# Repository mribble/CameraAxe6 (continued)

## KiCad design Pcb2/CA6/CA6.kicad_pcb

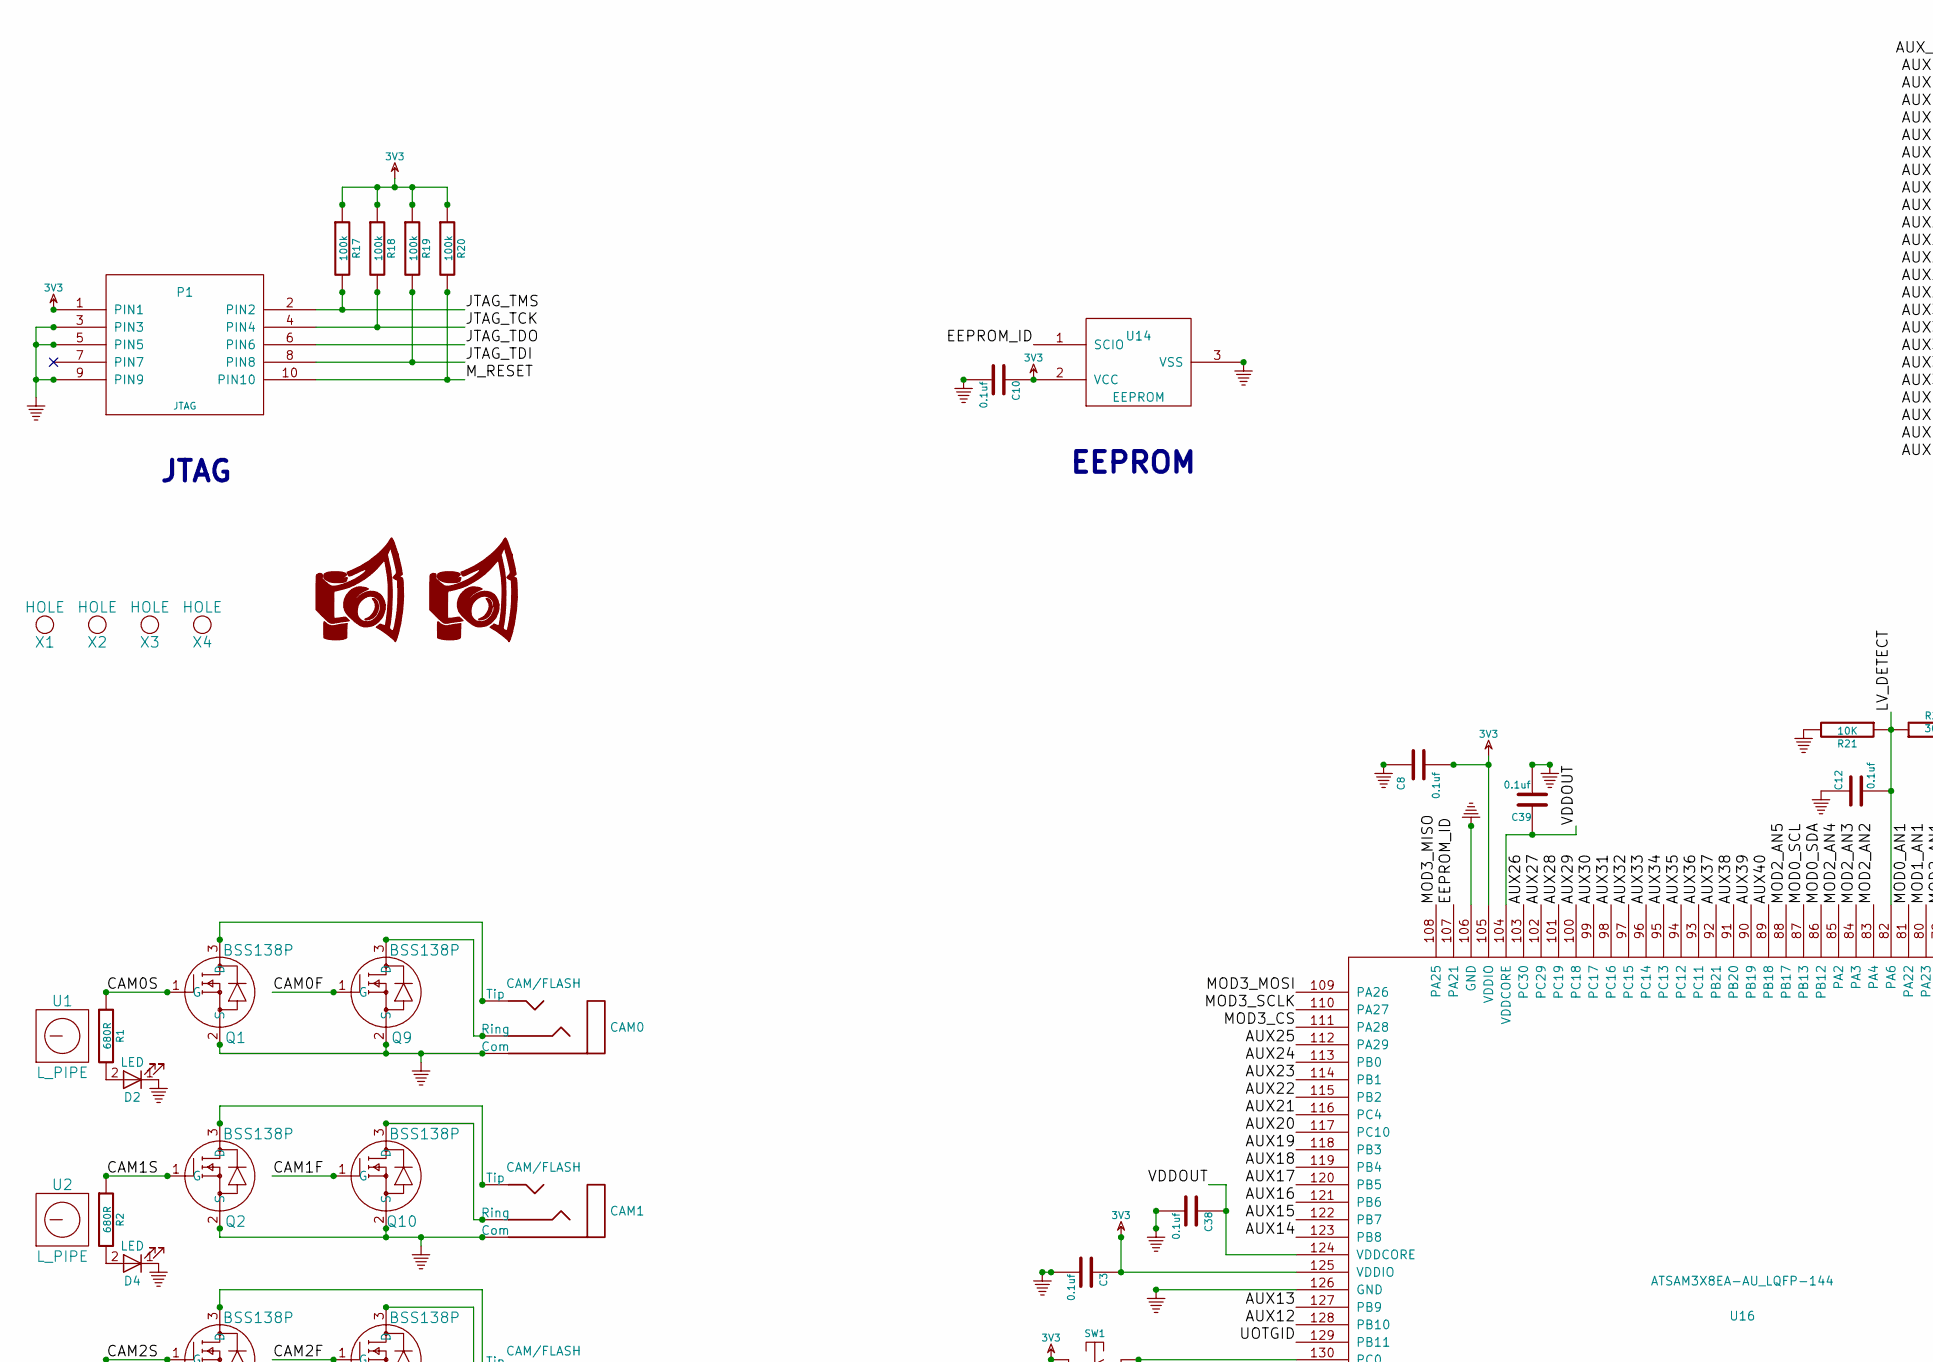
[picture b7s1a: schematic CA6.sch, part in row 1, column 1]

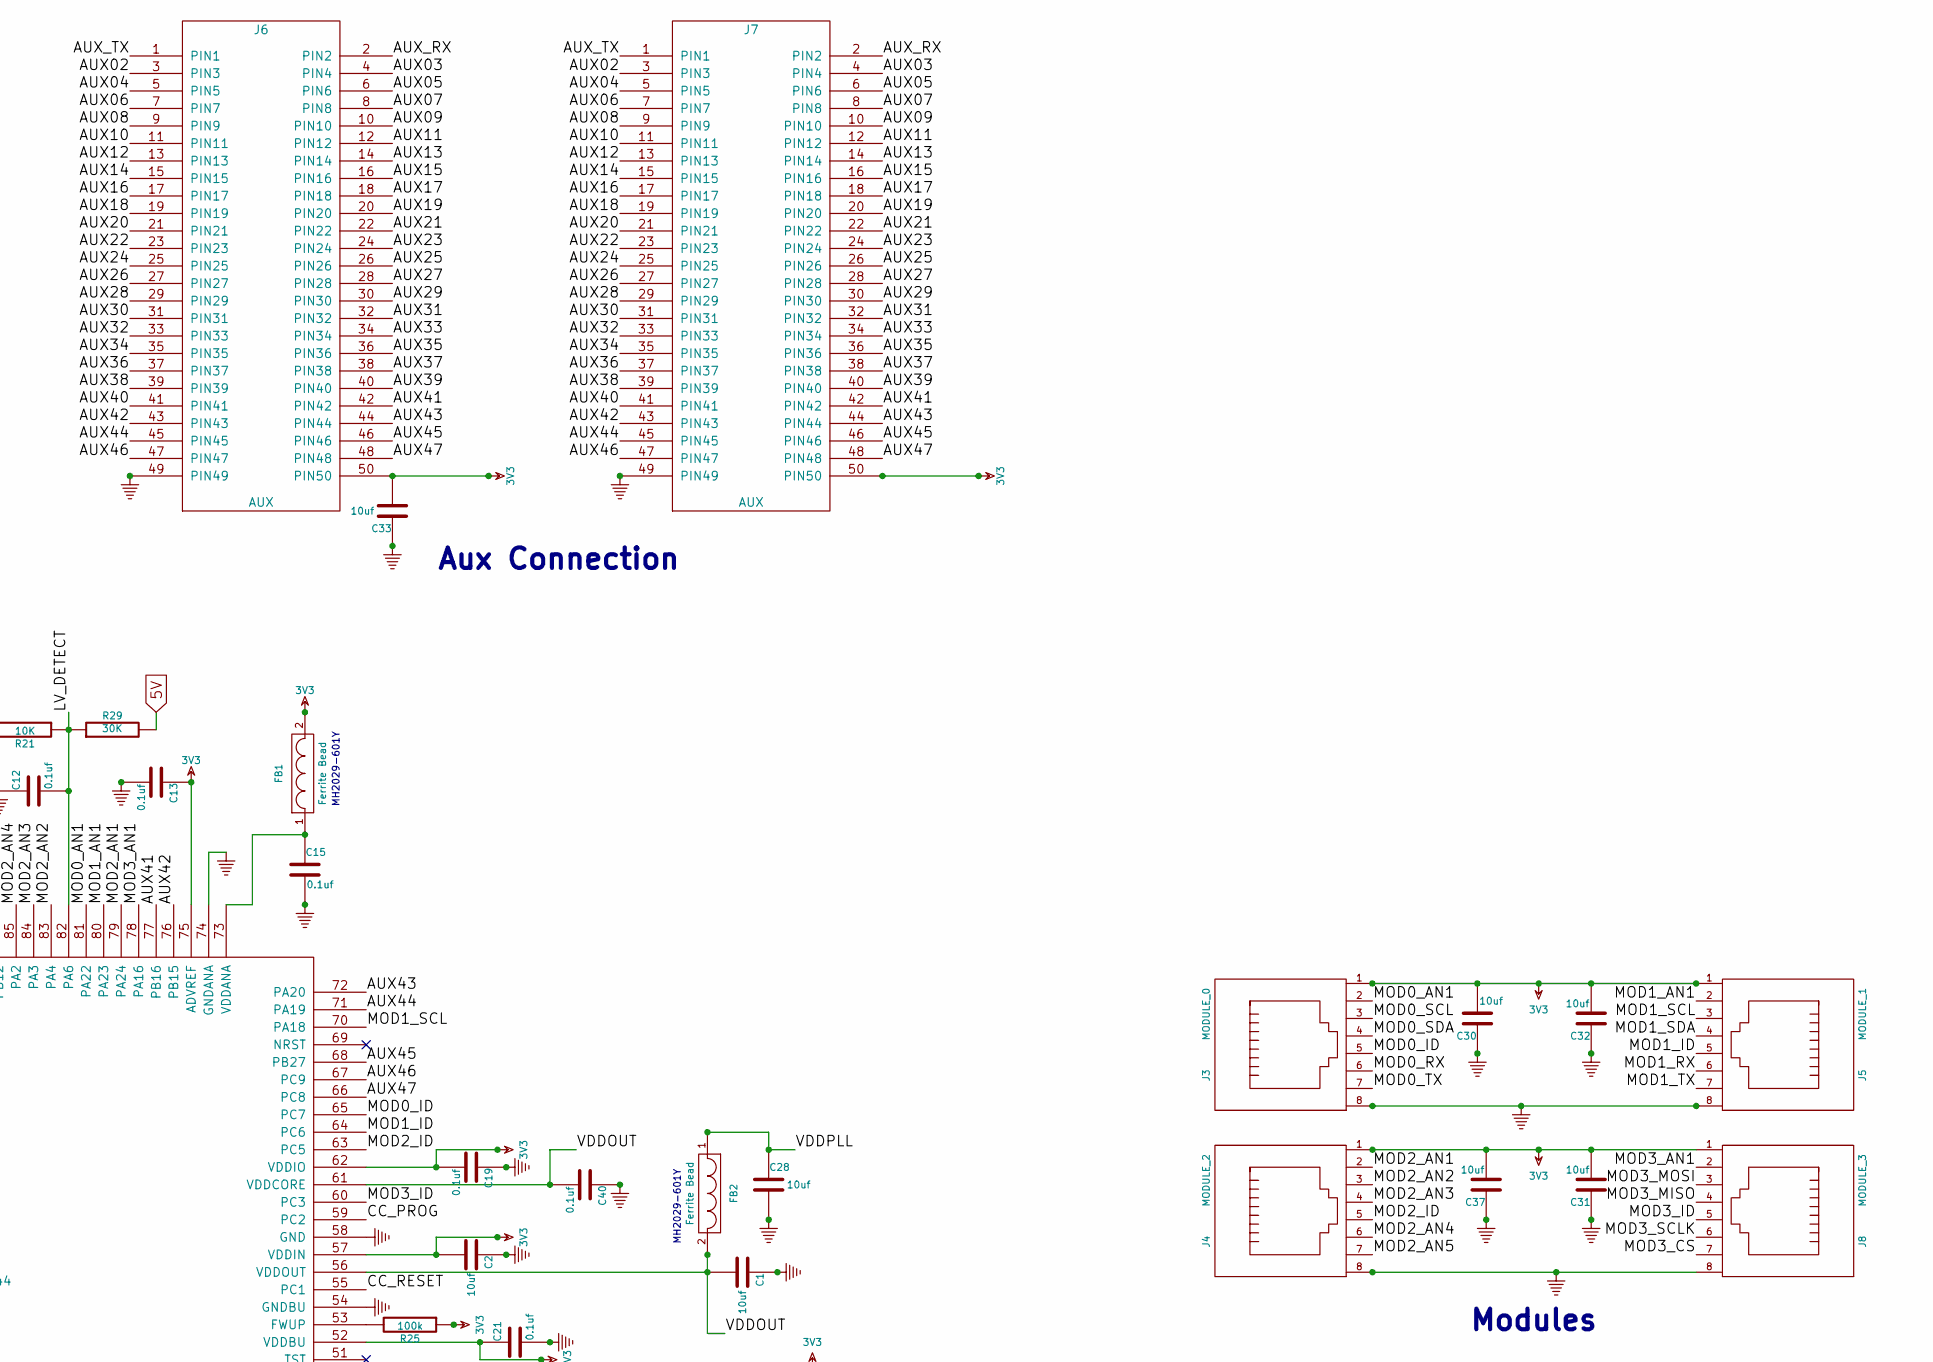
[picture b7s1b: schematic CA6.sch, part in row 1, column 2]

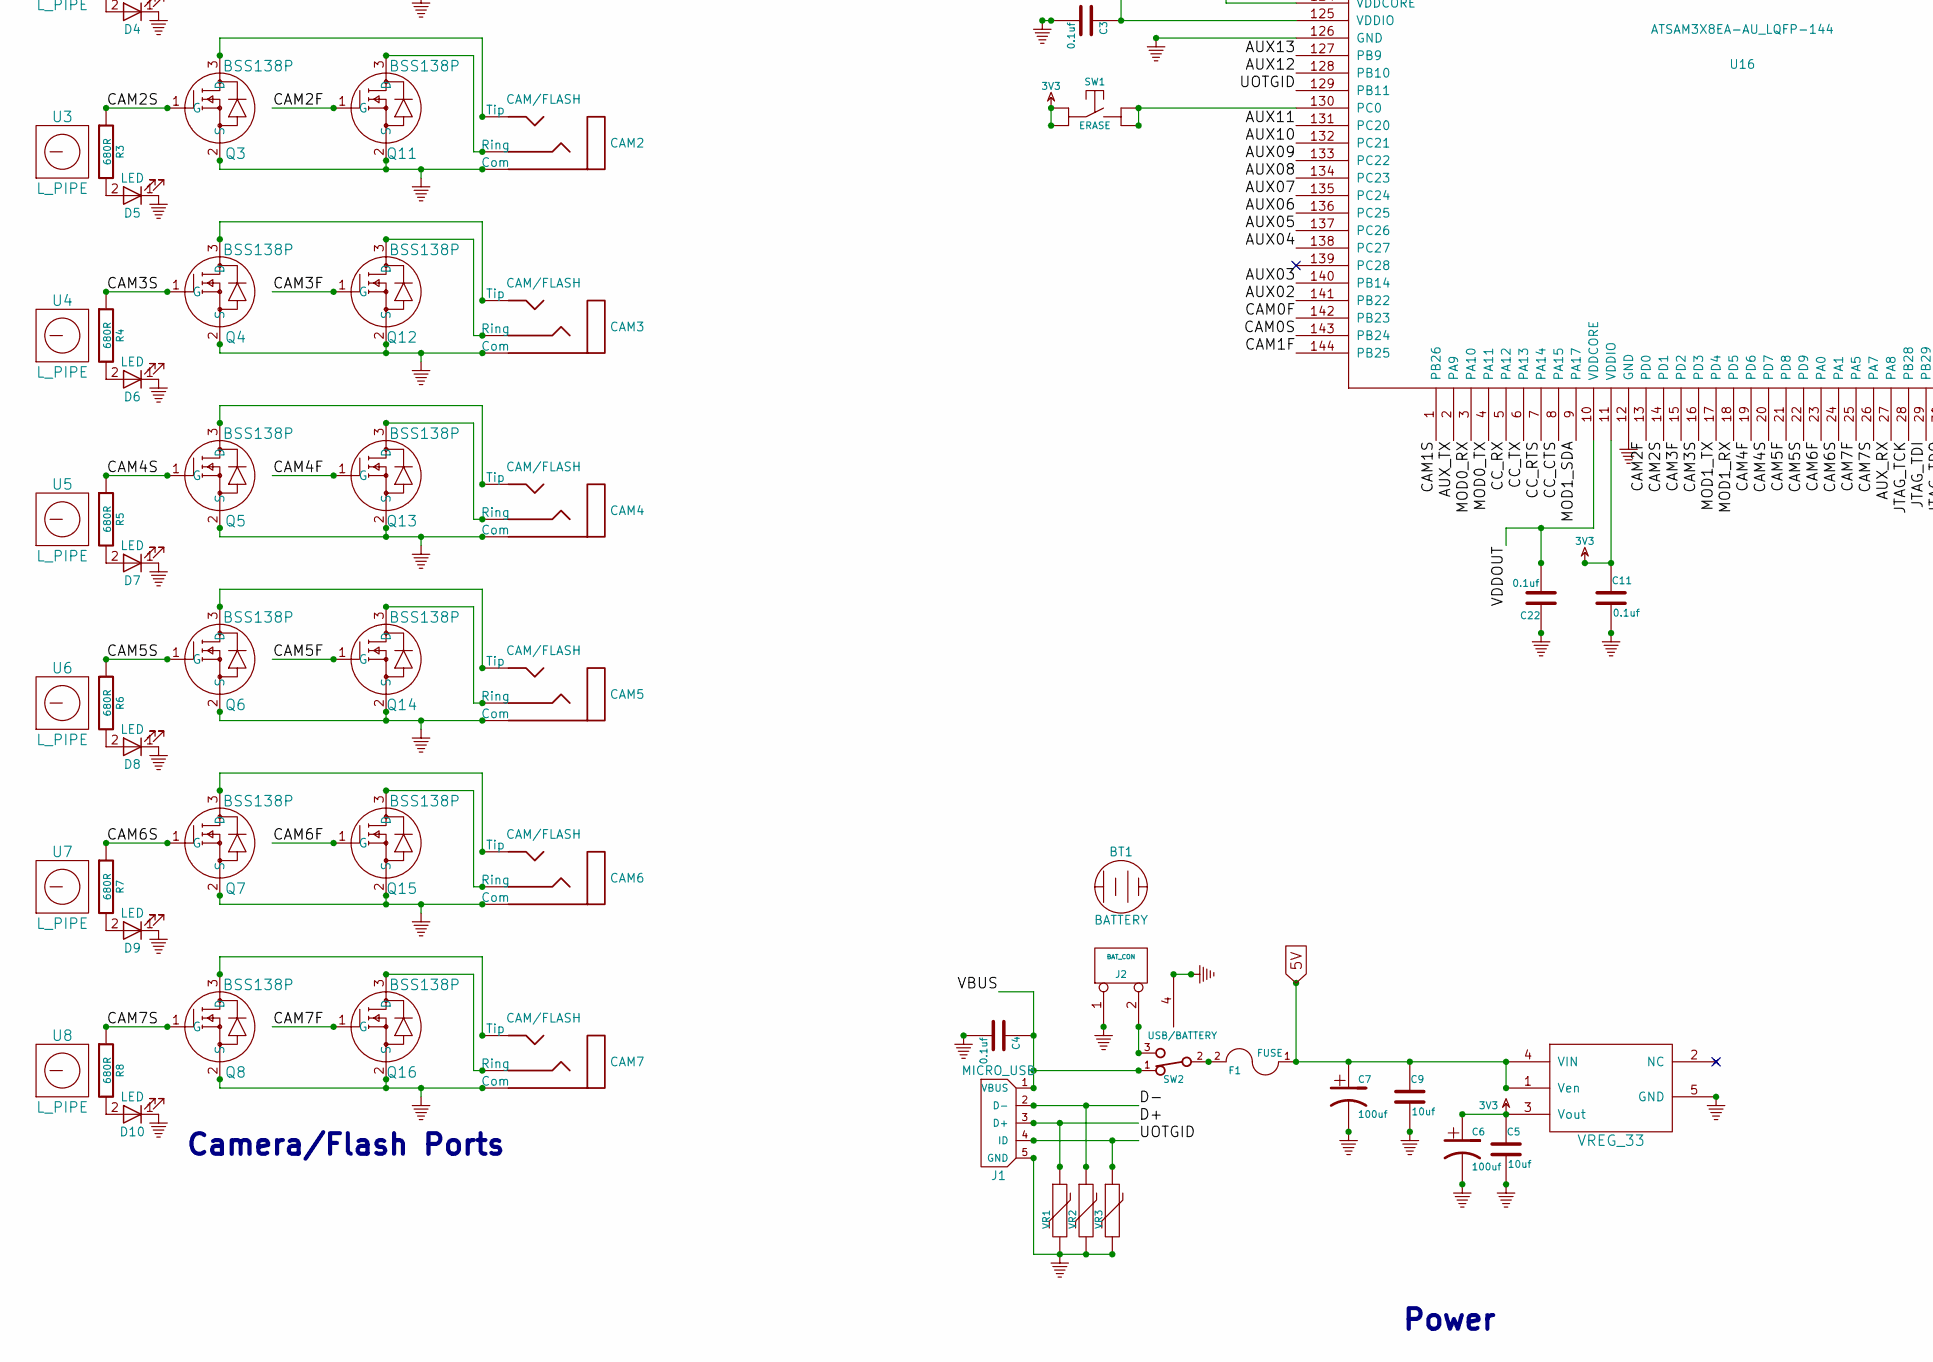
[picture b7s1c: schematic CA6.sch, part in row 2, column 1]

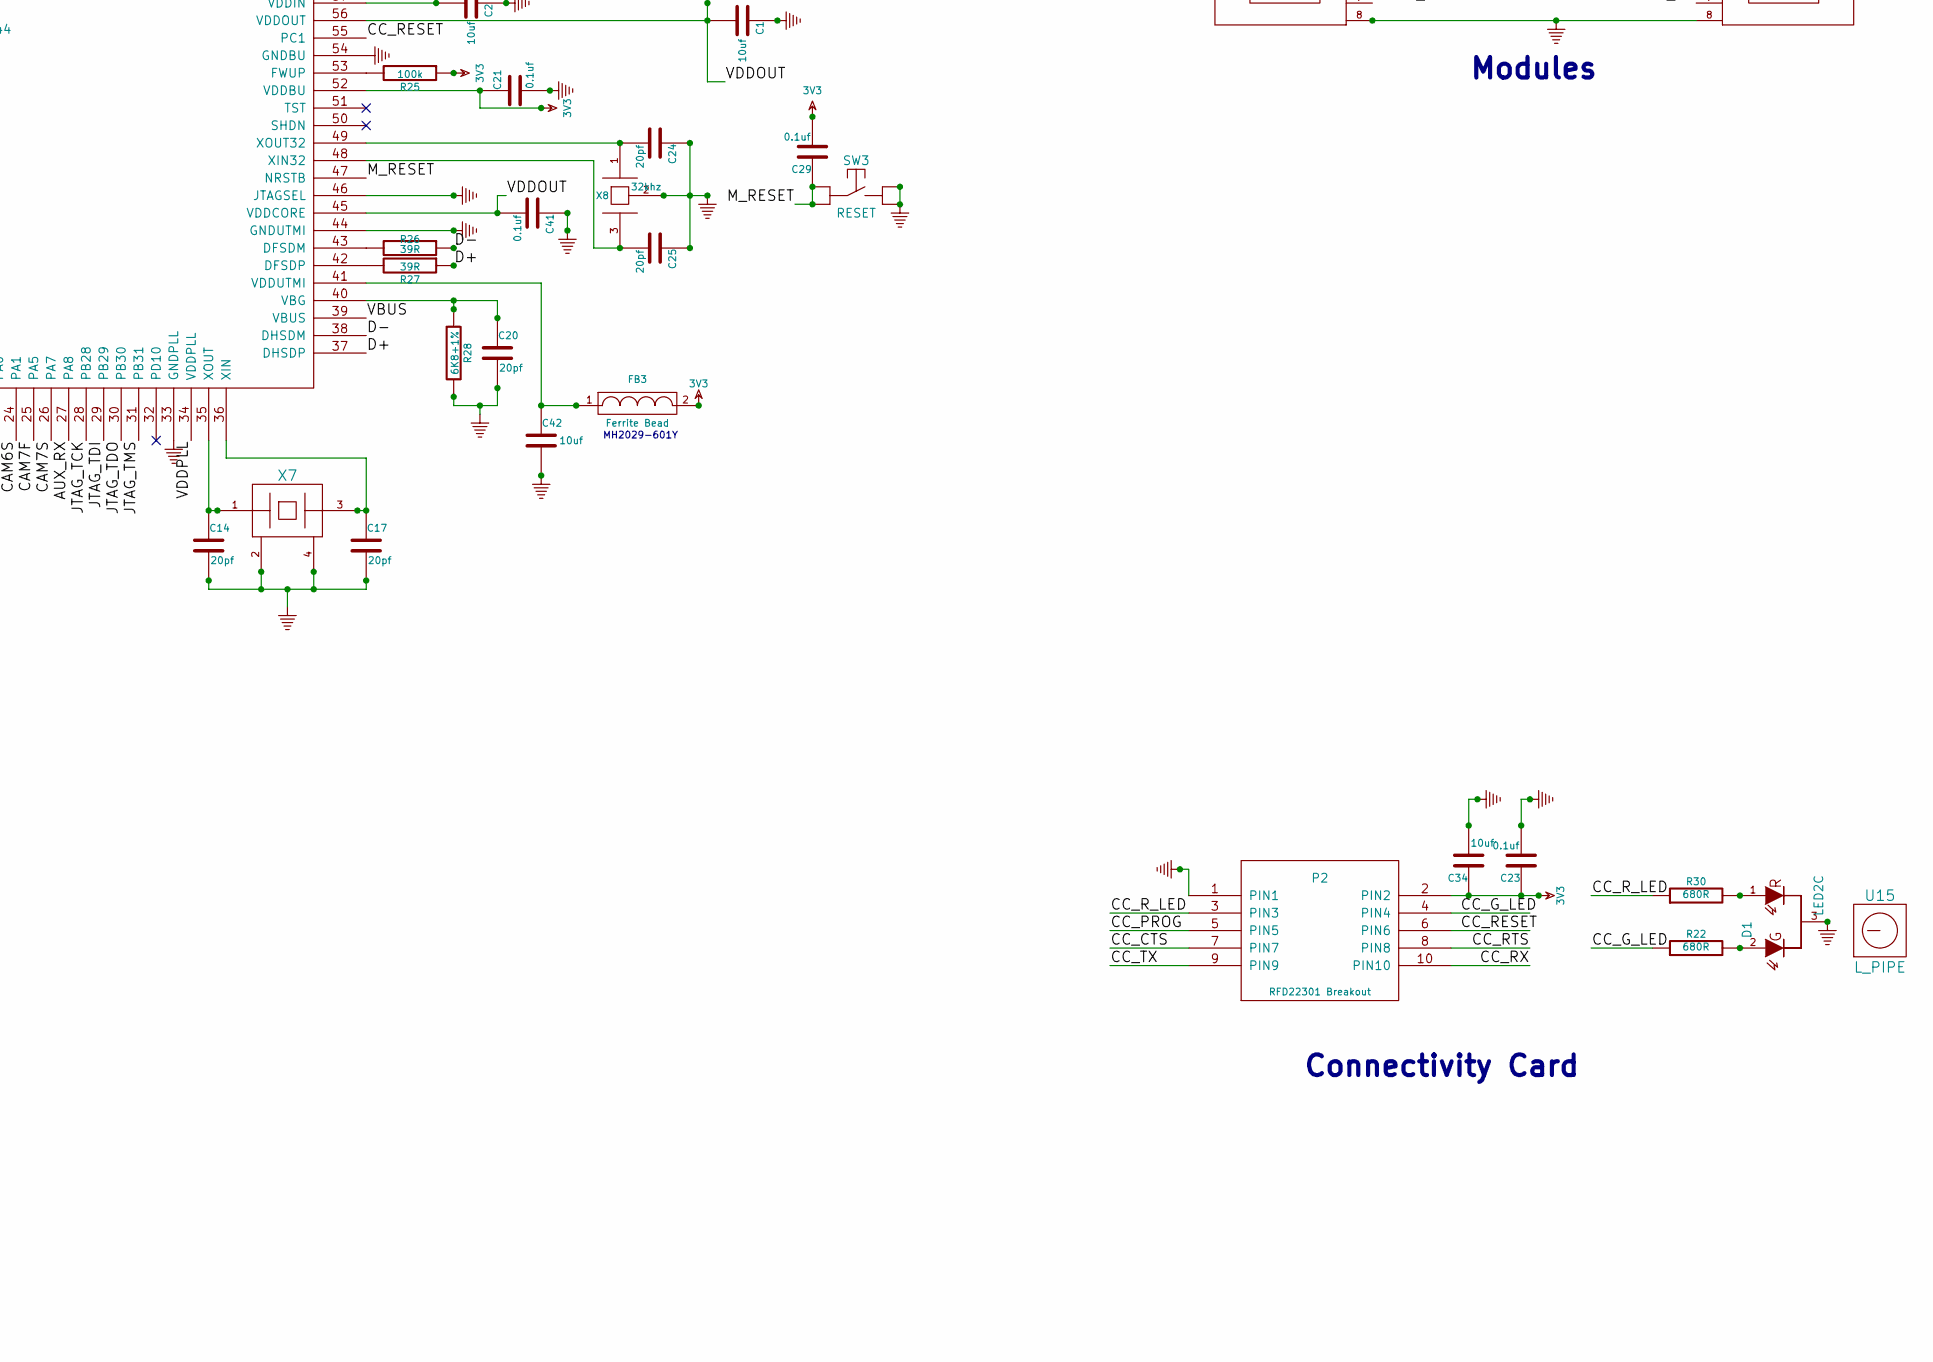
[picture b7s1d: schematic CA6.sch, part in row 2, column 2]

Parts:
BT1: BATTERY; BATTERY_4AA_12BH348-GR
C1, C2, C5, C9, C28, C30, C31, C32, C33, C34, C37, C42: 10uf; c_1206
C3, C4, C8, C10, C11, C12, C13, C15, C19, C21, C22, C23, C29, C38, C39, C40, C41: 0.1uf; c_0603
C6, C7: 100uf; c_elec_6.3x5.7
C14, C17, C20, C24, C25: 20pf; c_0603
CAM0, CAM1, CAM2, CAM3, CAM4, CAM5, CAM6, CAM7: CAM/FLASH; 161-3334-E_Big_Pad
D1: LED2C; LED-SOT-23
D2, D4, D5, D6, D7, D8, D9, D10: LED; LED_0805
F1: FUSE; SM1812
FB1, FB2, FB3: Ferrite Bead; SM0805
J1: MICRO_USB; USB_MICRO_10118194-0001LF
J2: BAT_CON; Screw_Terminal_Block_2P
J3: MODULE_0; RJ45_RJHSE-5080
J4: MODULE_2; RJ45_RJHSE-5080
J5: MODULE_1; RJ45_RJHSE-5080
J6: AUX; IDC_50PIN(2X25)-90
J7: AUX; IDC_50PIN(2X25)-M
J8: MODULE_3; RJ45_RJHSE-5080
LOGO1, LOGO2: CA_LOGO_150; CA_Logo_15mm
P1: JTAG; JTAG_20021121-00010C4LF
P2: RFD22301 Breakout; Socket_Strip_Straight_1x10_Pitch2.54mm
Q1, Q2, Q3, Q4, Q5, Q6, Q7, Q8, Q9, Q10, Q11, Q12, Q13, Q14, Q15, Q16: BSS138P; SOT23
R1, R2, R3, R4, R5, R6, R7, R8, R22, R30: 680R; SM0603_Resistor
R17, R18, R19, R20, R25: 100k; SM0603_Resistor
R21: 10K; SM0603_Resistor
R26, R27: 39R; SM0603_Resistor
R28: 6K8+1%; SM0603_Resistor
R29: 30K; SM0603_Resistor
SW1: ERASE; PTS645_throughhole
SW2: USB/BATTERY; EG_1224
SW3: RESET; PTS645_throughhole
U1, U2, U3, U4, U5, U6, U7, U8, U15: L_PIPE; SLP3-150-100-R
U12: VREG_33; SOT223-5
U14: EEPROM; SOT-23_11AA160
U16: ATSAM3X8EA-AU_LQFP-144; TQFP144
VR1, VR2, VR3: VR; SM0603
X1, X2, X3, X4: HOLE; HOLE_3.0mm
X7: CRYSTAL_4; CRYSTAL_ABM3B
X8: 32khz; AB26TRQ

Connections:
3V3: C2.2, C3.1, C5.1, C6.1, C8.2, C10.1, C11.1, C13.1, C19.2, C21.1, C23.1, C29.2, C30.2, C31.2, C32.2, C33.2, C34.1, C37.2, FB1.2, FB3.2, J3.1, J4.1, J5.1, J6.50 (PIN50), J7.50 (PIN50), J8.1, P1.1 (PIN1), P2.2 (PIN2), R17.1, R18.1, R19.1, R20.1, R25.1, SW1.1, SW1.2, U12.3 (Vout), U14.2 (VCC), U16.11 (VDDIO), U16.52 (VDDBU), U16.57 (VDDIN), U16.62 (VDDIO), U16.75 (ADVREF), U16.105 (VDDIO), U16.125 (VDDIO)
5V: C7.1, C9.1, F1.1, R29.2, U12.1 (Ven), U12.4 (VIN)
/AUX02: J6.3 (PIN3), J7.3 (PIN3), U16.141 (PB22)
/AUX03: J6.4 (PIN4), J7.4 (PIN4), U16.140 (PB14)
/AUX04: J6.5 (PIN5), J7.5 (PIN5), U16.138 (PC27)
/AUX05: J6.6 (PIN6), J7.6 (PIN6), U16.137 (PC26)
/AUX06: J6.7 (PIN7), J7.7 (PIN7), U16.136 (PC25)
/AUX07: J6.8 (PIN8), J7.8 (PIN8), U16.135 (PC24)
/AUX08: J6.9 (PIN9), J7.9 (PIN9), U16.134 (PC23)
/AUX09: J6.10 (PIN10), J7.10 (PIN10), U16.133 (PC22)
/AUX10: J6.11 (PIN11), J7.11 (PIN11), U16.132 (PC21)
/AUX11: J6.12 (PIN12), J7.12 (PIN12), U16.131 (PC20)
/AUX12: J6.13 (PIN13), J7.13 (PIN13), U16.128 (PB10)
/AUX13: J6.14 (PIN14), J7.14 (PIN14), U16.127 (PB9)
/AUX14: J6.15 (PIN15), J7.15 (PIN15), U16.123 (PB8)
/AUX15: J6.16 (PIN16), J7.16 (PIN16), U16.122 (PB7)
/AUX16: J6.17 (PIN17), J7.17 (PIN17), U16.121 (PB6)
/AUX17: J6.18 (PIN18), J7.18 (PIN18), U16.120 (PB5)
/AUX18: J6.19 (PIN19), J7.19 (PIN19), U16.119 (PB4)
/AUX19: J6.20 (PIN20), J7.20 (PIN20), U16.118 (PB3)
/AUX20: J6.21 (PIN21), J7.21 (PIN21), U16.117 (PC10)
/AUX21: J6.22 (PIN22), J7.22 (PIN22), U16.116 (PC4)
/AUX22: J6.23 (PIN23), J7.23 (PIN23), U16.115 (PB2)
/AUX23: J6.24 (PIN24), J7.24 (PIN24), U16.114 (PB1)
/AUX24: J6.25 (PIN25), J7.25 (PIN25), U16.113 (PB0)
/AUX25: J6.26 (PIN26), J7.26 (PIN26), U16.112 (PA29)
/AUX26: J6.27 (PIN27), J7.27 (PIN27), U16.103 (PC30)
/AUX27: J6.28 (PIN28), J7.28 (PIN28), U16.102 (PC29)
/AUX28: J6.29 (PIN29), J7.29 (PIN29), U16.101 (PC19)
/AUX29: J6.30 (PIN30), J7.30 (PIN30), U16.100 (PC18)
/AUX30: J6.31 (PIN31), J7.31 (PIN31), U16.99 (PC17)
/AUX31: J6.32 (PIN32), J7.32 (PIN32), U16.98 (PC16)
/AUX32: J6.33 (PIN33), J7.33 (PIN33), U16.97 (PC15)
/AUX33: J6.34 (PIN34), J7.34 (PIN34), U16.96 (PC14)
/AUX34: J6.35 (PIN35), J7.35 (PIN35), U16.95 (PC13)
/AUX35: J6.36 (PIN36), J7.36 (PIN36), U16.94 (PC12)
/AUX36: J6.37 (PIN37), J7.37 (PIN37), U16.93 (PC11)
/AUX37: J6.38 (PIN38), J7.38 (PIN38), U16.92 (PB21)
/AUX38: J6.39 (PIN39), J7.39 (PIN39), U16.91 (PB20)
/AUX39: J6.40 (PIN40), J7.40 (PIN40), U16.90 (PB19)
/AUX40: J6.41 (PIN41), J7.41 (PIN41), U16.89 (PB18)
/AUX41: J6.42 (PIN42), J7.42 (PIN42), U16.77 (PB16)
/AUX42: J6.43 (PIN43), J7.43 (PIN43), U16.76 (PB15)
/AUX43: J6.44 (PIN44), J7.44 (PIN44), U16.72 (PA20)
/AUX44: J6.45 (PIN45), J7.45 (PIN45), U16.71 (PA19)
/AUX45: J6.46 (PIN46), J7.46 (PIN46), U16.68 (PB27)
/AUX46: J6.47 (PIN47), J7.47 (PIN47), U16.67 (PC9)
/AUX47: J6.48 (PIN48), J7.48 (PIN48), U16.66 (PC8)
/AUX_RX: J6.2 (PIN2), J7.2 (PIN2), U16.27 (PA8)
/AUX_TX: J6.1 (PIN1), J7.1 (PIN1), U16.2 (PA9)
/CAM0F: Q9.1 (G), U16.142 (PB23)
/CAM0S: Q1.1 (G), R1.1, U16.143 (PB24)
/CAM1F: Q10.1 (G), U16.144 (PB25)
/CAM1S: Q2.1 (G), R2.1, U16.1 (PB26)
/CAM2F: Q11.1 (G), U16.13 (PD0)
/CAM2S: Q3.1 (G), R3.1, U16.14 (PD1)
/CAM3F: Q12.1 (G), U16.15 (PD2)
/CAM3S: Q4.1 (G), R4.1, U16.16 (PD3)
/CAM4F: Q13.1 (G), U16.19 (PD6)
/CAM4S: Q5.1 (G), R5.1, U16.20 (PD7)
/CAM5F: Q14.1 (G), U16.21 (PD8)
/CAM5S: Q6.1 (G), R6.1, U16.22 (PD9)
/CAM6F: Q15.1 (G), U16.23 (PA0)
/CAM6S: Q7.1 (G), R7.1, U16.24 (PA1)
/CAM7F: Q16.1 (G), U16.25 (PA5)
/CAM7S: Q8.1 (G), R8.1, U16.26 (PA7)
/CC_CTS: P2.7 (PIN7), U16.8 (PA15)
/CC_G_LED: P2.4 (PIN4), R22.1
/CC_PROG: P2.5 (PIN5), U16.59 (PC2)
/CC_RESET: P2.6 (PIN6), U16.55 (PC1)
/CC_RTS: P2.8 (PIN8), U16.7 (PA14)
/CC_RX: P2.10 (PIN10), U16.5 (PA12)
/CC_R_LED: P2.3 (PIN3), R30.1
/CC_TX: P2.9 (PIN9), U16.6 (PA13)
/D+: J1.3 (D+), R27.1, U16.37 (DHSDP), VR1.1
/D-: J1.2 (D-), R26.1, U16.38 (DHSDM), VR2.1
/EEPROM_ID: U14.1 (SCIO), U16.107 (PA21)
/JTAG_TCK: P1.4 (PIN4), R18.2, U16.28 (PB28)
/JTAG_TDI: P1.8 (PIN8), R19.2, U16.29 (PB29)
/JTAG_TDO: P1.6 (PIN6), U16.30 (PB30)
/JTAG_TMS: P1.2 (PIN2), R17.2, U16.31 (PB31)
/LV_DETECT: C12.2, R21.1, R29.1, U16.82 (PA6)
/MOD0_AN1: J3.2, U16.81 (PA22)
/MOD0_ID: J3.5, U16.65 (PC7)
/MOD0_RX: J3.6, U16.3 (PA10)
/MOD0_SCL: J3.3, U16.87 (PB13)
/MOD0_SDA: J3.4, U16.86 (PB12)
/MOD0_TX: J3.7, U16.4 (PA11)
/MOD1_AN1: J5.2, U16.80 (PA23)
/MOD1_ID: J5.5, U16.64 (PC6)
/MOD1_RX: J5.6, U16.18 (PD5)
/MOD1_SCL: J5.3, U16.70 (PA18)
/MOD1_SDA: J5.4, U16.9 (PA17)
/MOD1_TX: J5.7, U16.17 (PD4)
/MOD2_AN1: J4.2, U16.79 (PA24)
/MOD2_AN2: J4.3, U16.83 (PA4)
/MOD2_AN3: J4.4, U16.84 (PA3)
/MOD2_AN4: J4.6, U16.85 (PA2)
/MOD2_AN5: J4.7, U16.88 (PB17)
/MOD2_ID: J4.5, U16.63 (PC5)
/MOD3_AN1: J8.2, U16.78 (PA16)
/MOD3_CS: J8.7, U16.111 (PA28)
/MOD3_ID: J8.5, U16.60 (PC3)
/MOD3_MISO: J8.4, U16.108 (PA25)
/MOD3_MOSI: J8.3, U16.109 (PA26)
/MOD3_SCLK: J8.6, U16.110 (PA27)
/M_RESET: C29.1, P1.10 (PIN10), R20.2, SW3.1, SW3.2, U16.47 (NRSTB)
/UOTGID: J1.4 (ID), U16.129 (PB11), VR3.1
/VBUS: C4.1, J1.1 (VBUS), SW2.1, U16.39 (VBUS)
/VDDOUT: C1.2, C22.2, C38.1, C39.1, C40.2, C41.2, FB2.2, U16.10 (VDDCORE), U16.45 (VDDCORE), U16.56 (VDDOUT), U16.61 (VDDCORE), U16.104 (VDDCORE), U16.124 (VDDCORE)
/VDDPLL: C28.1, FB2.1, U16.34 (VDDPLL)
GND: C1.1, C2.1, C3.2, C4.2, C5.2, C6.2, C7.2, C8.1, C9.2, C10.2, C11.2, C12.1, C13.2, C14.2, C15.2, C17.2, C19.1, C20.2, C21.2, C22.1, C23.2, C24.1, C25.1, C28.2, C30.1, C31.1, C32.1, C33.1, C34.2, C37.1, C38.2, C39.2, C40.1, C41.1, C42.2, CAM0.3 (Com), CAM1.3 (Com), CAM2.3 (Com), CAM3.3 (Com), CAM4.3 (Com), CAM5.3 (Com), CAM6.3 (Com), CAM7.3 (Com), D1.3, D2.1 (K), D4.1 (K), D5.1 (K), D6.1 (K), D7.1 (K), D8.1 (K), D9.1 (K), D10.1 (K), J1.5 (GND), J2.1, J3.8, J4.8, J5.8, J6.49 (PIN49), J7.49 (PIN49), J8.8, P1.3 (PIN3), P1.5 (PIN5), P1.9 (PIN9), P2.1 (PIN1), Q1.2 (S), Q2.2 (S), Q3.2 (S), Q4.2 (S), Q5.2 (S), Q6.2 (S), Q7.2 (S), Q8.2 (S), Q9.2 (S), Q10.2 (S), Q11.2 (S), Q12.2 (S), Q13.2 (S), Q14.2 (S), Q15.2 (S), Q16.2 (S), R21.2, R28.2, SW2.4 (Gnd), SW3.3, SW3.4, U12.5 (GND), U14.3 (VSS), U16.12 (GND), U16.33 (GNDPLL), U16.44 (GNDUTMI), U16.46 (JTAGSEL), U16.54 (GNDBU), U16.58 (GND), U16.74 (GNDANA), U16.106 (GND), U16.126 (GND), VR1.2, VR2.2, VR3.2, X7.2, X7.4, X8.2
unnamed: C14.1, U16.35 (XOUT), X7.1
unnamed: C15.1, FB1.1, U16.73 (VDDANA)
unnamed: C17.1, U16.36 (XIN), X7.3
unnamed: C20.1, R28.1, U16.40 (VBG)
unnamed: C24.2, U16.49 (XOUT32), X8.1
unnamed: C25.2, U16.48 (XIN32), X8.3
unnamed: C42.1, FB3.1, U16.41 (VDDUTMI)
unnamed: CAM0.1 (Ring), Q9.3 (D)
unnamed: CAM0.2 (Tip), Q1.3 (D)
unnamed: CAM1.1 (Ring), Q10.3 (D)
unnamed: CAM1.2 (Tip), Q2.3 (D)
unnamed: CAM2.1 (Ring), Q11.3 (D)
unnamed: CAM2.2 (Tip), Q3.3 (D)
unnamed: CAM3.1 (Ring), Q12.3 (D)
unnamed: CAM3.2 (Tip), Q4.3 (D)
unnamed: CAM4.1 (Ring), Q13.3 (D)
unnamed: CAM4.2 (Tip), Q5.3 (D)
unnamed: CAM5.1 (Ring), Q14.3 (D)
unnamed: CAM5.2 (Tip), Q6.3 (D)
unnamed: CAM6.1 (Ring), Q15.3 (D)
unnamed: CAM6.2 (Tip), Q7.3 (D)
unnamed: CAM7.1 (Ring), Q16.3 (D)
unnamed: CAM7.2 (Tip), Q8.3 (D)
unnamed: D1.1, R30.2
unnamed: D1.2, R22.2
unnamed: D2.2 (A), R1.2
unnamed: D4.2 (A), R2.2
unnamed: D5.2 (A), R3.2
unnamed: D6.2 (A), R4.2
unnamed: D7.2 (A), R5.2
unnamed: D8.2 (A), R6.2
unnamed: D9.2 (A), R7.2
unnamed: D10.2 (A), R8.2
unnamed: F1.2, SW2.2
unnamed: J2.2 (PM), SW2.3
unnamed: R25.2, U16.53 (FWUP)
unnamed: R26.2, U16.43 (DFSDM)
unnamed: R27.2, U16.42 (DFSDP)
unnamed: SW1.3, SW1.4, U16.130 (PC0)

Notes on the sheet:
Modules
MH2029-601Y
Aux Connection
EEPROM
Camera/Flash Ports
JTAG
Connectivity Card
Power

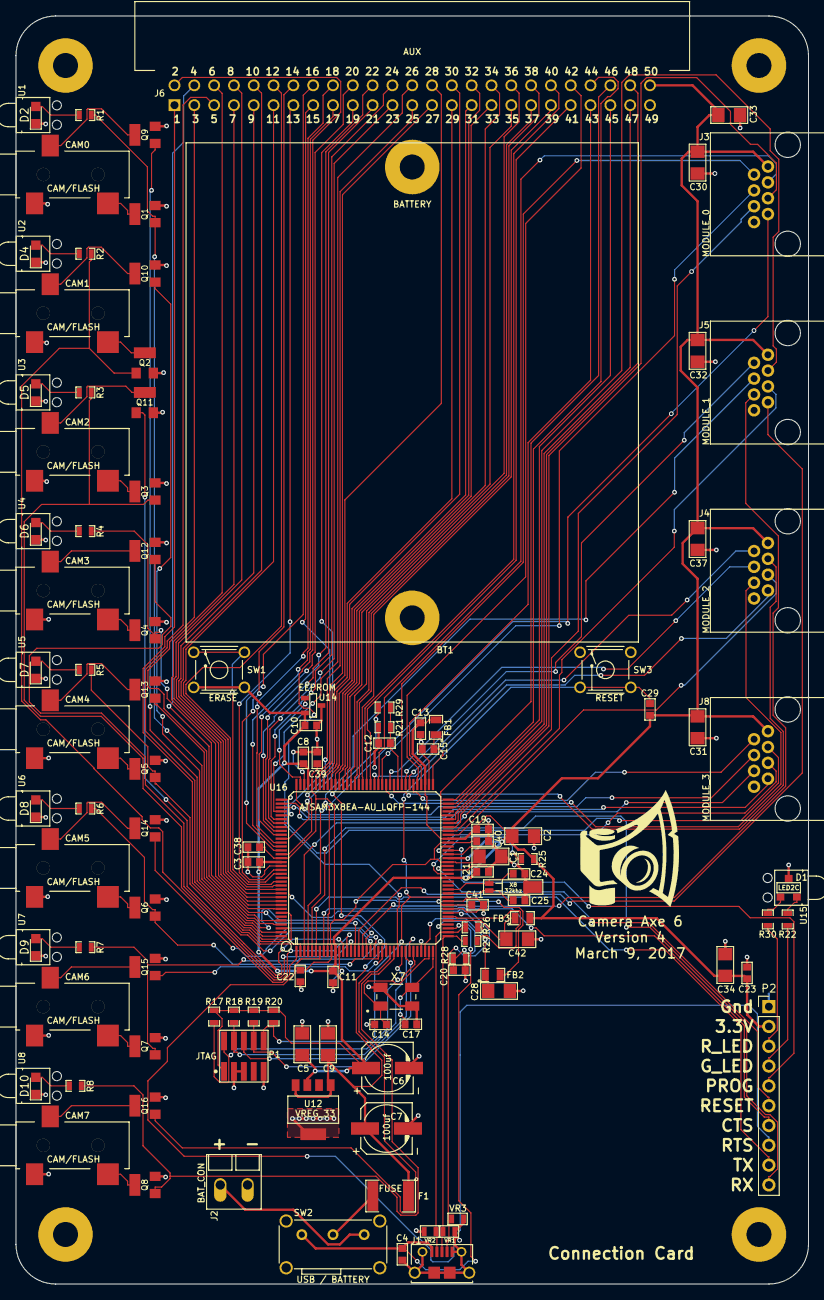
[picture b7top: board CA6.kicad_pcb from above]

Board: 2 copper layers, 101.6 x 162.6 mm, 129 parts (1 on the bottom side), 151 nets.
